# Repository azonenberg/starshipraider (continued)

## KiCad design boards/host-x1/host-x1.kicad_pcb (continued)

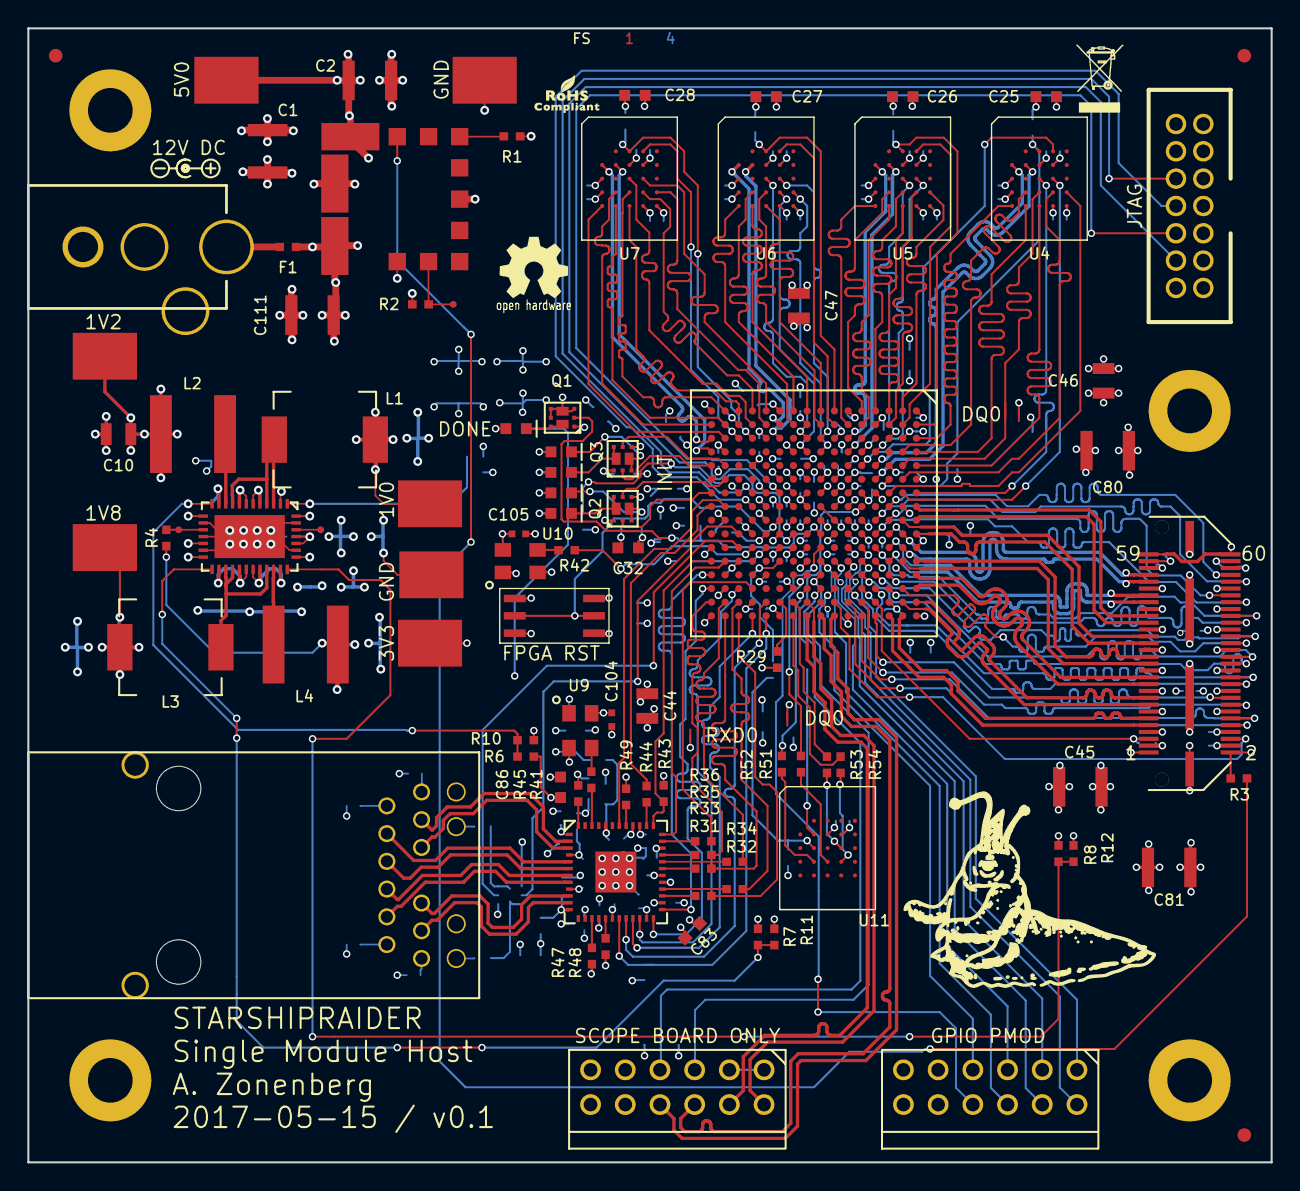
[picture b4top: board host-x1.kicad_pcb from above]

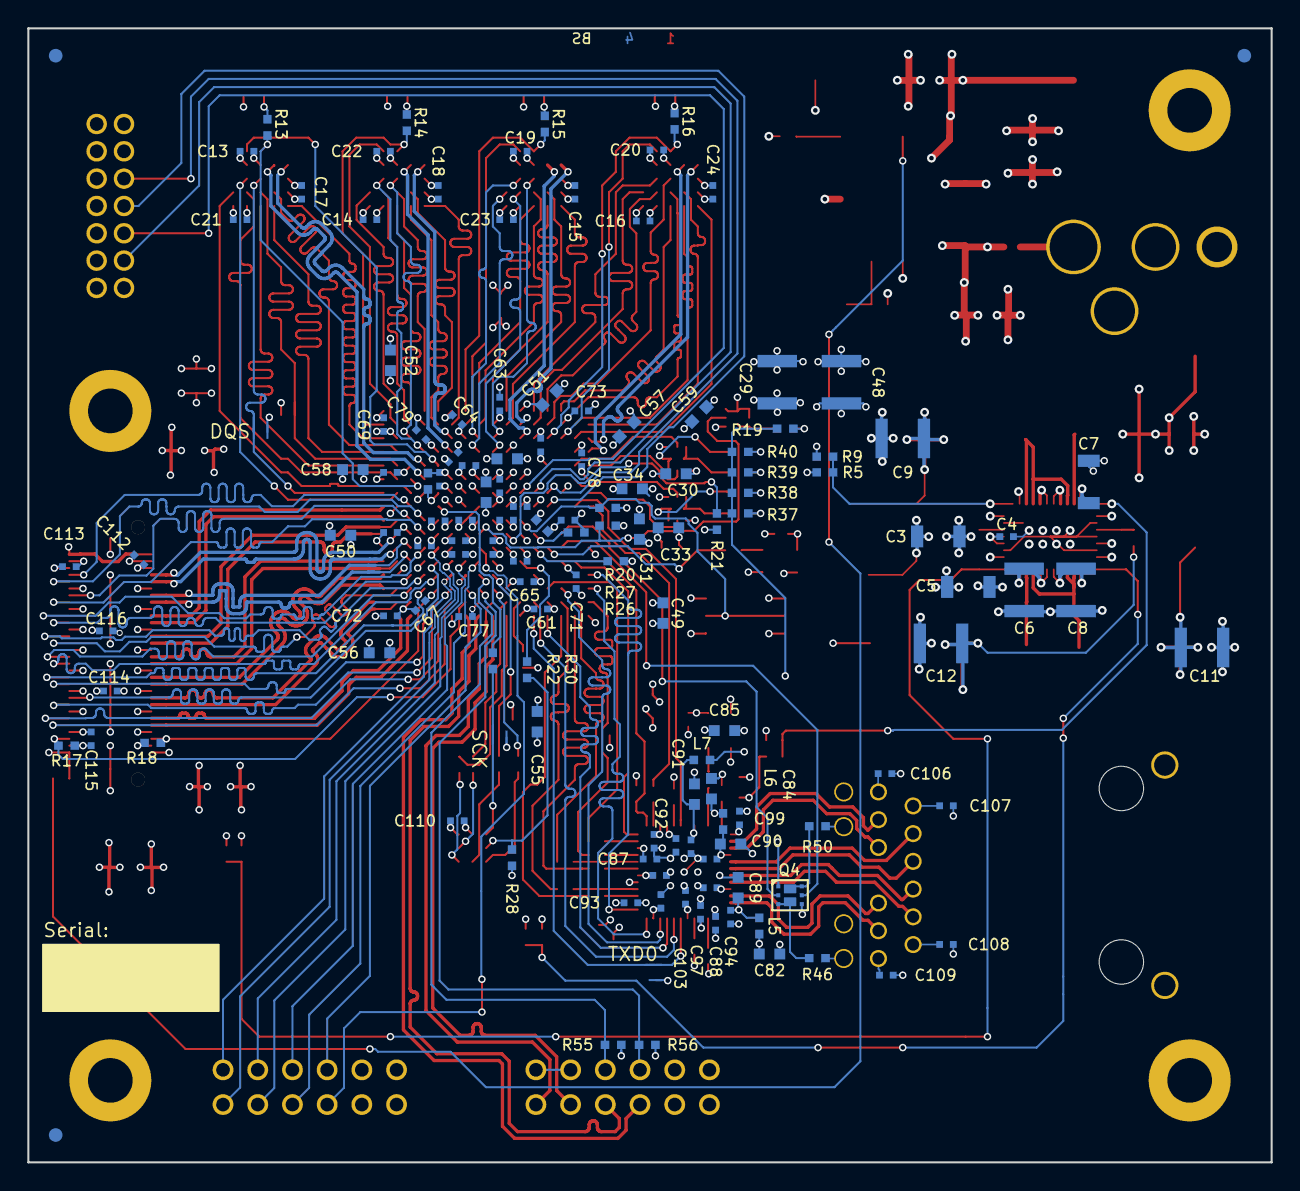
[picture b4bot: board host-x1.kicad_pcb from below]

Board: 4 copper layers, 91.0 x 83.0 mm, 251 parts (139 on the bottom side), 212 nets.

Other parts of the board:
C116: 0.1 uF; EIA_0402_CAP_NOSILK
FIDUCIAL_1MM, FIDUCIAL_1MM#2, FIDUCIAL_1MM#3, FIDUCIAL_1MM#4, FIDUCIAL_1MM#5, FIDUCIAL_1MM#6: VAL**; FIDUCIAL_1MM
M1: LOGO; LONGTHING-600DPI
M2: LOGO_ROHS; Logo_silk_ROHS_5x2.8mm
M3: LOGO_WEEE; Logo_silk_WEEE_3.4x5mm
M4, M5, M6, M7: HOLE; MECHANICAL_CLEARANCEHOLE_4_40

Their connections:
/3V3: C116.1; also elsewhere on the board
/GND: C116.2; also elsewhere on the board

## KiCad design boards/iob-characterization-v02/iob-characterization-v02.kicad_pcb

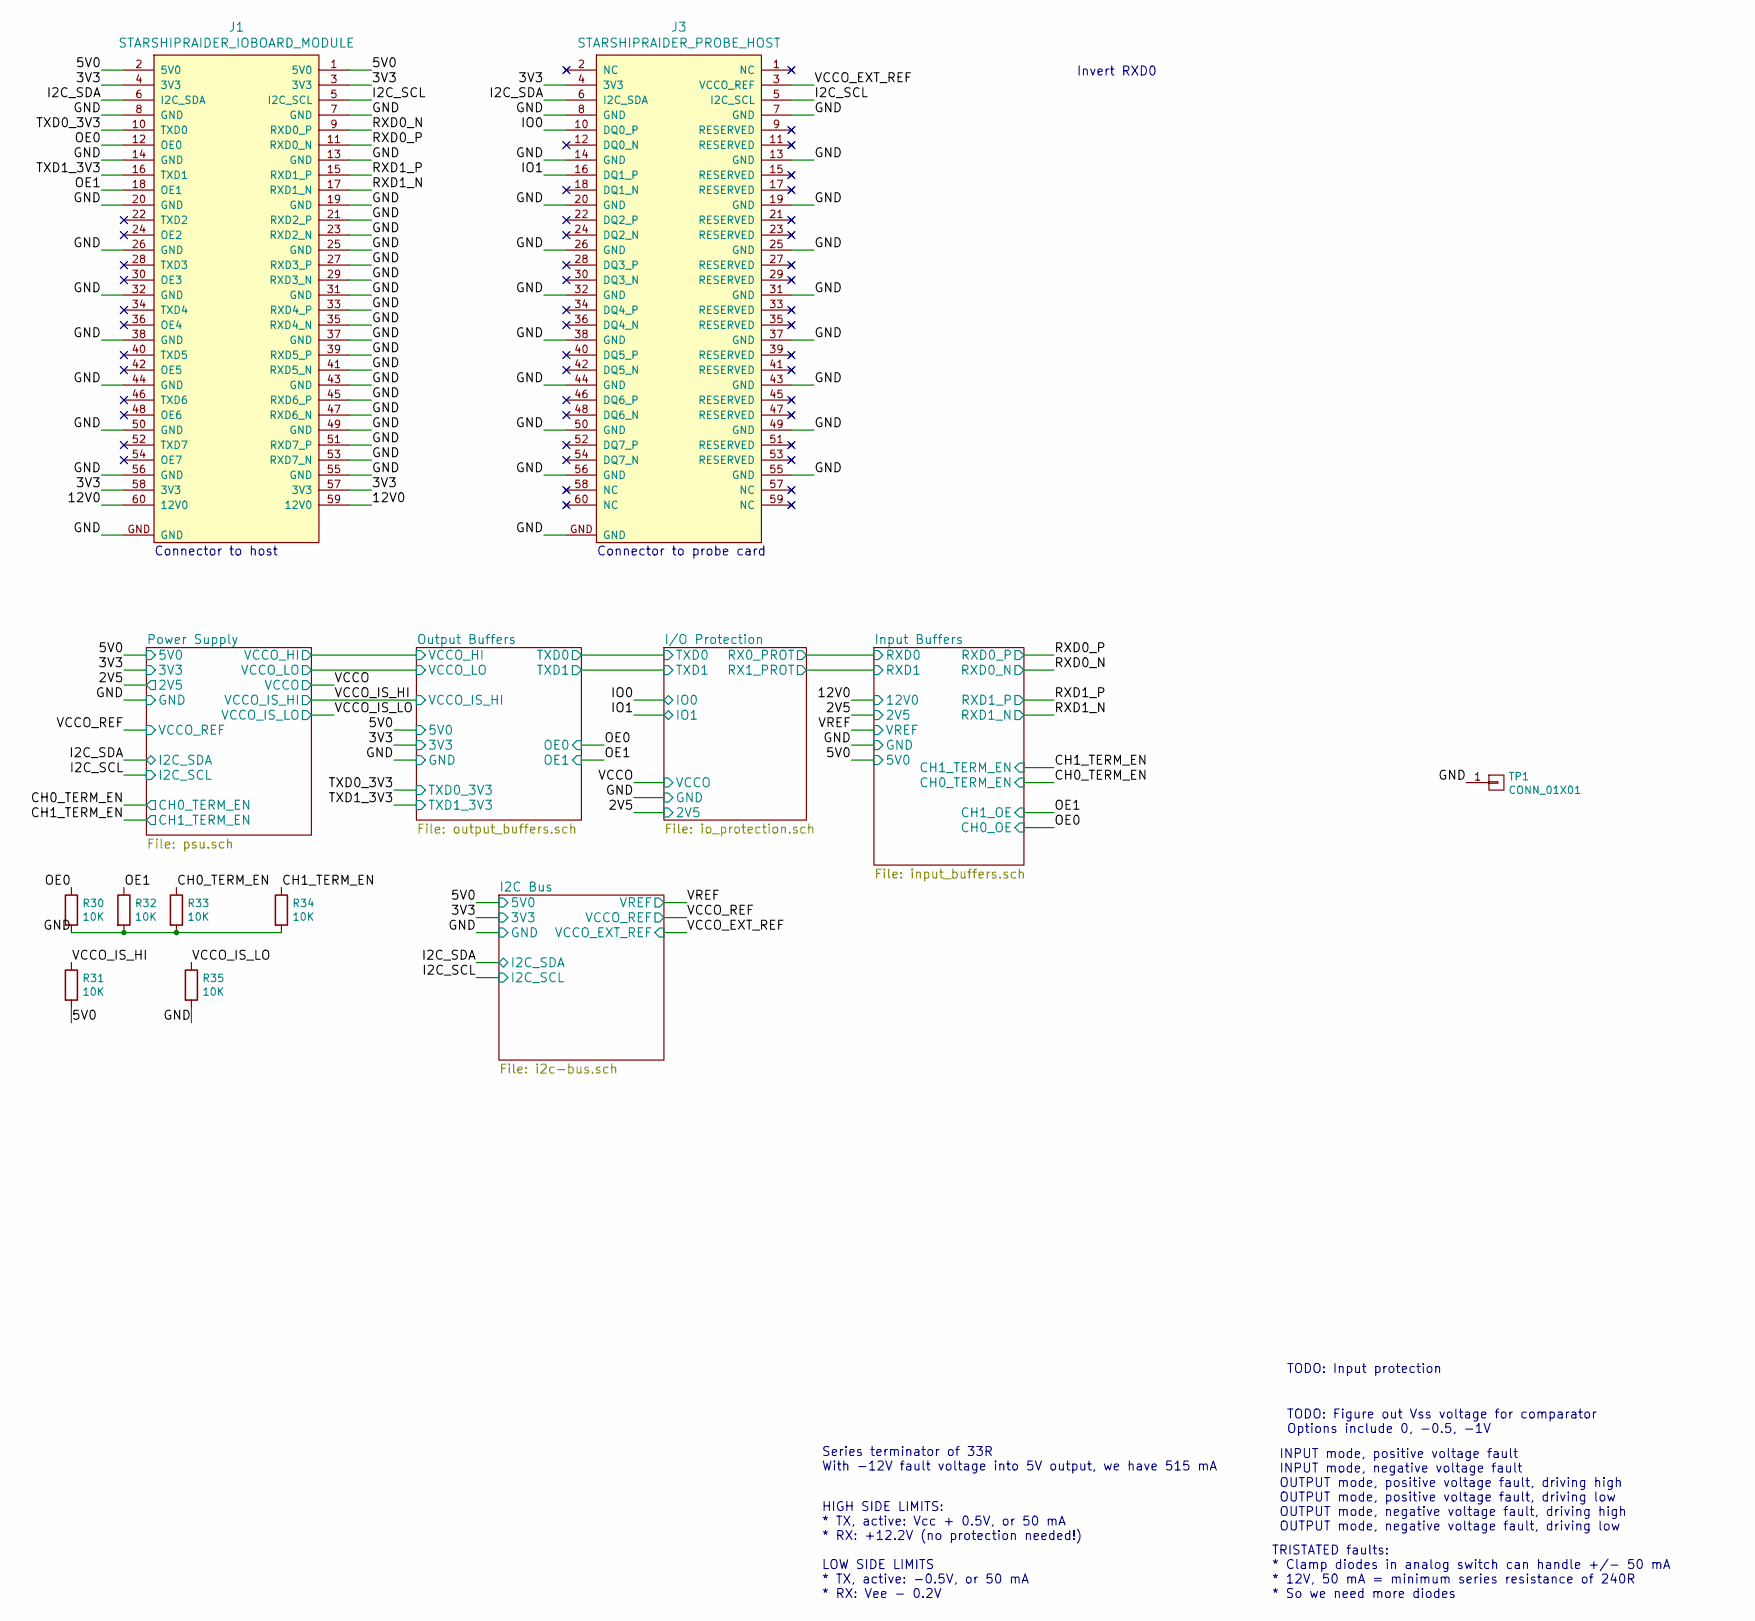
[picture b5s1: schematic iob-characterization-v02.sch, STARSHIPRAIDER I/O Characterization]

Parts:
J1: STARSHIPRAIDER_IOBOARD_MODULE; CONN_SAMTEC_QSH-030-01-L-D-A
J3: STARSHIPRAIDER_PROBE_HOST; CONN_SAMTEC_QTH-030-01-L-D-A
R30, R31, R32, R33, R34, R35: 10K; EIA_0402_RES_NOSILK
TP1: CONN_01X01; TESTPOINT_SMT_KEYSTONE_5016

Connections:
/3V3: J1.3 (3V3), J1.4 (3V3), J1.57 (3V3), J1.58 (3V3), J3.4 (3V3); also elsewhere on the board
/5V0: J1.1 (5V0), J1.2 (5V0), R31.2; also elsewhere on the board
/12V0: J1.59 (12V0), J1.60 (12V0); also elsewhere on the board
/CH0_TERM_EN: R33.1; also elsewhere on the board
/CH1_TERM_EN: R34.1; also elsewhere on the board
/GND: J1.7 (GND), J1.8 (GND), J1.13 (GND), J1.14 (GND), J1.19 (GND), J1.20 (GND), J1.21 (RXD2_P), J1.23 (RXD2_N), J1.25 (GND), J1.26 (GND), J1.27 (RXD3_P), J1.29 (RXD3_N), J1.31 (GND), J1.32 (GND), J1.33 (RXD4_P), J1.35 (RXD4_N), J1.37 (GND), J1.38 (GND), J1.39 (RXD5_P), J1.41 (RXD5_N), J1.43 (GND), J1.44 (GND), J1.45 (RXD6_P), J1.47 (RXD6_N), J1.49 (GND), J1.50 (GND), J1.51 (RXD7_P), J1.53 (RXD7_N), J1.55 (GND), J1.56 (GND), J1.GND, J3.7 (GND), J3.8 (GND), J3.13 (GND), J3.14 (GND), J3.19 (GND), J3.20 (GND), J3.25 (GND), J3.26 (GND), J3.31 (GND), J3.32 (GND), J3.37 (GND), J3.38 (GND), J3.43 (GND), J3.44 (GND), J3.49 (GND), J3.50 (GND), J3.55 (GND), J3.56 (GND), J3.GND, R30.2, R32.2, R33.2, R34.2, R35.2, TP1.1; also elsewhere on the board
/I2C_SCL: J1.5 (I2C_SCL), J3.5 (I2C_SCL); also elsewhere on the board
/I2C_SDA: J1.6 (I2C_SDA), J3.6 (I2C_SDA); also elsewhere on the board
/IO0: J3.10 (DQ0_P); also elsewhere on the board
/IO1: J3.16 (DQ1_P); also elsewhere on the board
/OE0: J1.12 (OE0), R30.1; also elsewhere on the board
/OE1: J1.18 (OE1), R32.1; also elsewhere on the board
/RXD0_N: J1.9 (RXD0_P); also elsewhere on the board
/RXD0_P: J1.11 (RXD0_N); also elsewhere on the board
/RXD1_N: J1.17 (RXD1_N); also elsewhere on the board
/RXD1_P: J1.15 (RXD1_P); also elsewhere on the board
/TXD0_3V3: J1.10 (TXD0); also elsewhere on the board
/TXD1_3V3: J1.16 (TXD1); also elsewhere on the board
/VCCO_EXT_REF: J3.3 (VCCO_REF); also elsewhere on the board
/VCCO_IS_HI: R31.1; also elsewhere on the board
/VCCO_IS_LO: R35.1; also elsewhere on the board

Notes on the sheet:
TODO: Input protection
TODO: Figure out Vss voltage for comparator Options include 0, -0.5, -1V
Connector to host
Connector to probe card
INPUT mode, positive voltage fault INPUT mode, negative voltage fault OUTPUT mode, positive voltage fault, driving high OUTPUT mode, positive voltage fault, driving low OUTPUT mode, negative voltage fault, driving high OUTPUT mode, negative voltage fault, driving low
TRISTATED faults: * Clamp diodes in analog switch can handle +/- 50 mA * 12V, 50 mA = minimum series resistance of 240R * So we need more diodes
Series terminator of 33R With -12V fault voltage into 5V output, we have 515 mA
HIGH SIDE LIMITS: * TX, active: Vcc + 0.5V, or 50 mA * RX: +12.2V (no protection needed!) LOW SIDE LIMITS * TX, active: -0.5V, or 50 mA * RX: Vee - 0.2V
Invert RXD0

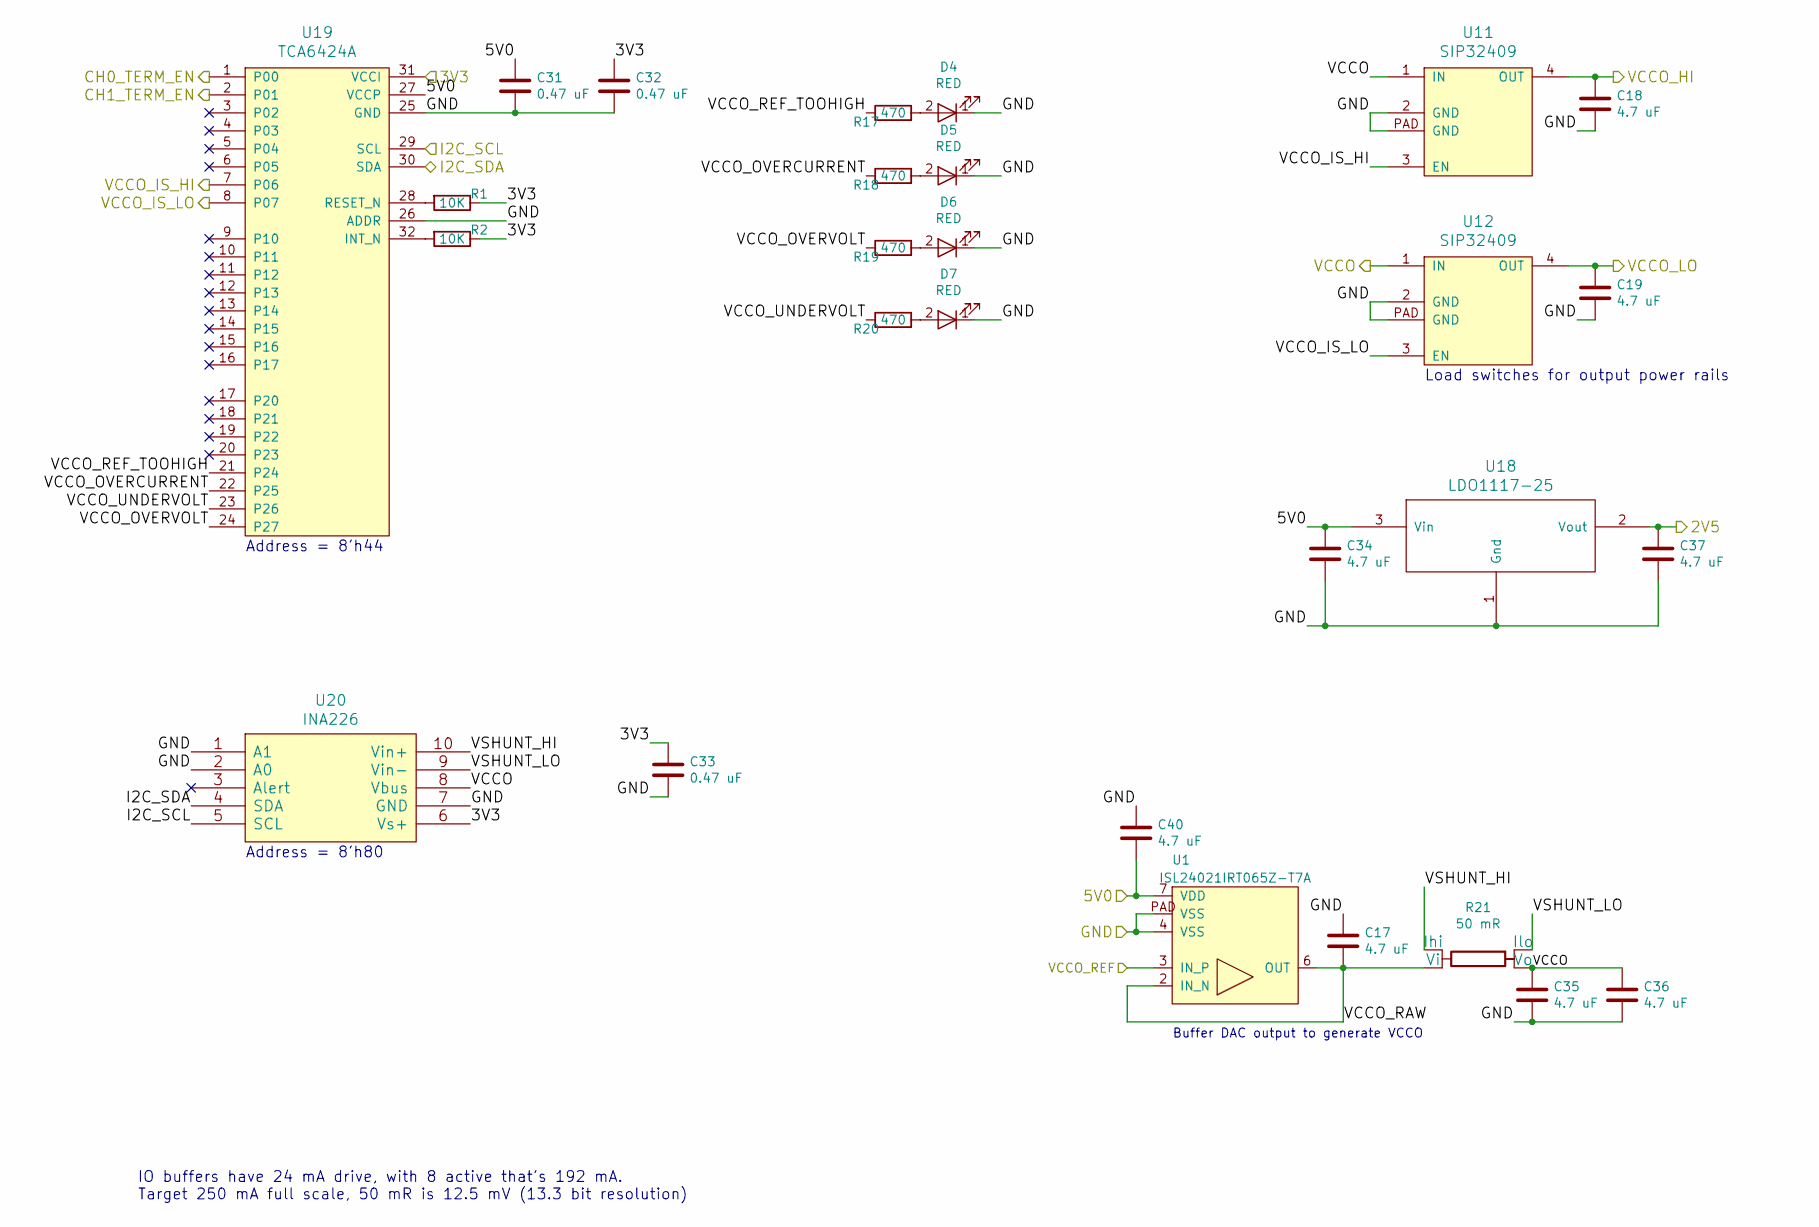
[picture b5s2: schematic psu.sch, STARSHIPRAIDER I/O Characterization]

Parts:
C17, C18, C19, C34, C35, C36, C37, C40: 4.7 uF; EIA_0603_CAP_NOSILK
C31, C32, C33: 0.47 uF; EIA_0402_CAP_NOSILK
D4, D5, D6, D7: RED; EIA_0603_LED
R1, R2: 10K; EIA_0402_CAP_NOSILK
R17, R18, R19, R20: 470; EIA_0402_RES_NOSILK
R21: 50 mR; OHMITE_LVK12
U1: ISL24021IRT065Z-T7A‎; DFN_8_0.65MM_3x3MM
U11, U12: SIP32409; DFN_4_0.5MM_1.6x1.2MM
U18: LDO1117-25; SOT223-4
U19: TCA6424A; QFN_32_0.5MM_5x5MM
U20: INA226; SOP_10_0.5MM_3MM

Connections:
/2V5: C37.1, U18.2 (Vout); also elsewhere on the board
/3V3: C32.1, C33.1, R1.1, R2.1, U19.31 (VCCI), U20.6 (Vs+); also elsewhere on the board
/5V0: C31.1, C34.1, C40.2, U1.7 (VDD), U18.3 (Vin), U19.27 (VCCP); also elsewhere on the board
/CH0_TERM_EN: U19.1 (P00); also elsewhere on the board
/CH1_TERM_EN: U19.2 (P01); also elsewhere on the board
/GND: C17.1, C18.2, C19.2, C31.2, C32.2, C33.2, C34.2, C35.2, C36.2, C37.2, C40.1, D4.1 (K), D5.1 (K), D6.1 (K), D7.1 (K), U1.4 (VSS), U1.PAD (VSS), U11.2 (GND), U11.PAD (GND), U12.2 (GND), U12.PAD (GND), U18.1 (Gnd), U19.25 (GND), U19.26 (ADDR), U20.1 (A1), U20.2 (A0), U20.7 (GND); also elsewhere on the board
/I2C_SCL: U19.29 (SCL), U20.5 (SCL); also elsewhere on the board
/I2C_SDA: U19.30 (SDA), U20.4 (SDA); also elsewhere on the board
/Output Buffers/VCCO_HI: C18.1, U11.4 (OUT); also elsewhere on the board
/Output Buffers/VCCO_LO: C19.1, U12.4 (OUT); also elsewhere on the board
/Power Supply/VCCO_OVERCURRENT: R18.1, U19.22 (P25)
/Power Supply/VCCO_OVERVOLT: R19.1, U19.24 (P27)
/Power Supply/VCCO_RAW: C17.2, R21.4 (Vi), U1.2 (IN_N), U1.6 (OUT)
/Power Supply/VCCO_REF_TOOHIGH: R17.1, U19.21 (P24)
/Power Supply/VCCO_UNDERVOLT: R20.1, U19.23 (P26)
/Power Supply/VSHUNT_HI: R21.3 (Ihi), U20.10 (Vin+)
/Power Supply/VSHUNT_LO: R21.1 (Ilo), U20.9 (Vin-)
/VCCO: C35.1, C36.1, R21.2 (Vo), U11.1 (IN), U12.1 (IN), U20.8 (Vbus); also elsewhere on the board
/VCCO_IS_HI: U11.3 (EN), U19.7 (P06); also elsewhere on the board
/VCCO_IS_LO: U12.3 (EN), U19.8 (P07); also elsewhere on the board
/VCCO_REF: U1.3 (IN_P); also elsewhere on the board
unnamed: D4.2 (A), R17.2
unnamed: D5.2 (A), R18.2
unnamed: D6.2 (A), R19.2
unnamed: D7.2 (A), R20.2
unnamed: R1.2, U19.28 (RESET_N)
unnamed: R2.2, U19.32 (INT_N)

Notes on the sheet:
Load switches for output power rails
Buffer DAC output to generate VCCO
Address = 8'h44
IO buffers have 24 mA drive, with 8 active that's 192 mA. Target 250 mA full scale, 50 mR is 12.5 mV (13.3 bit resolution)
Address = 8'h80

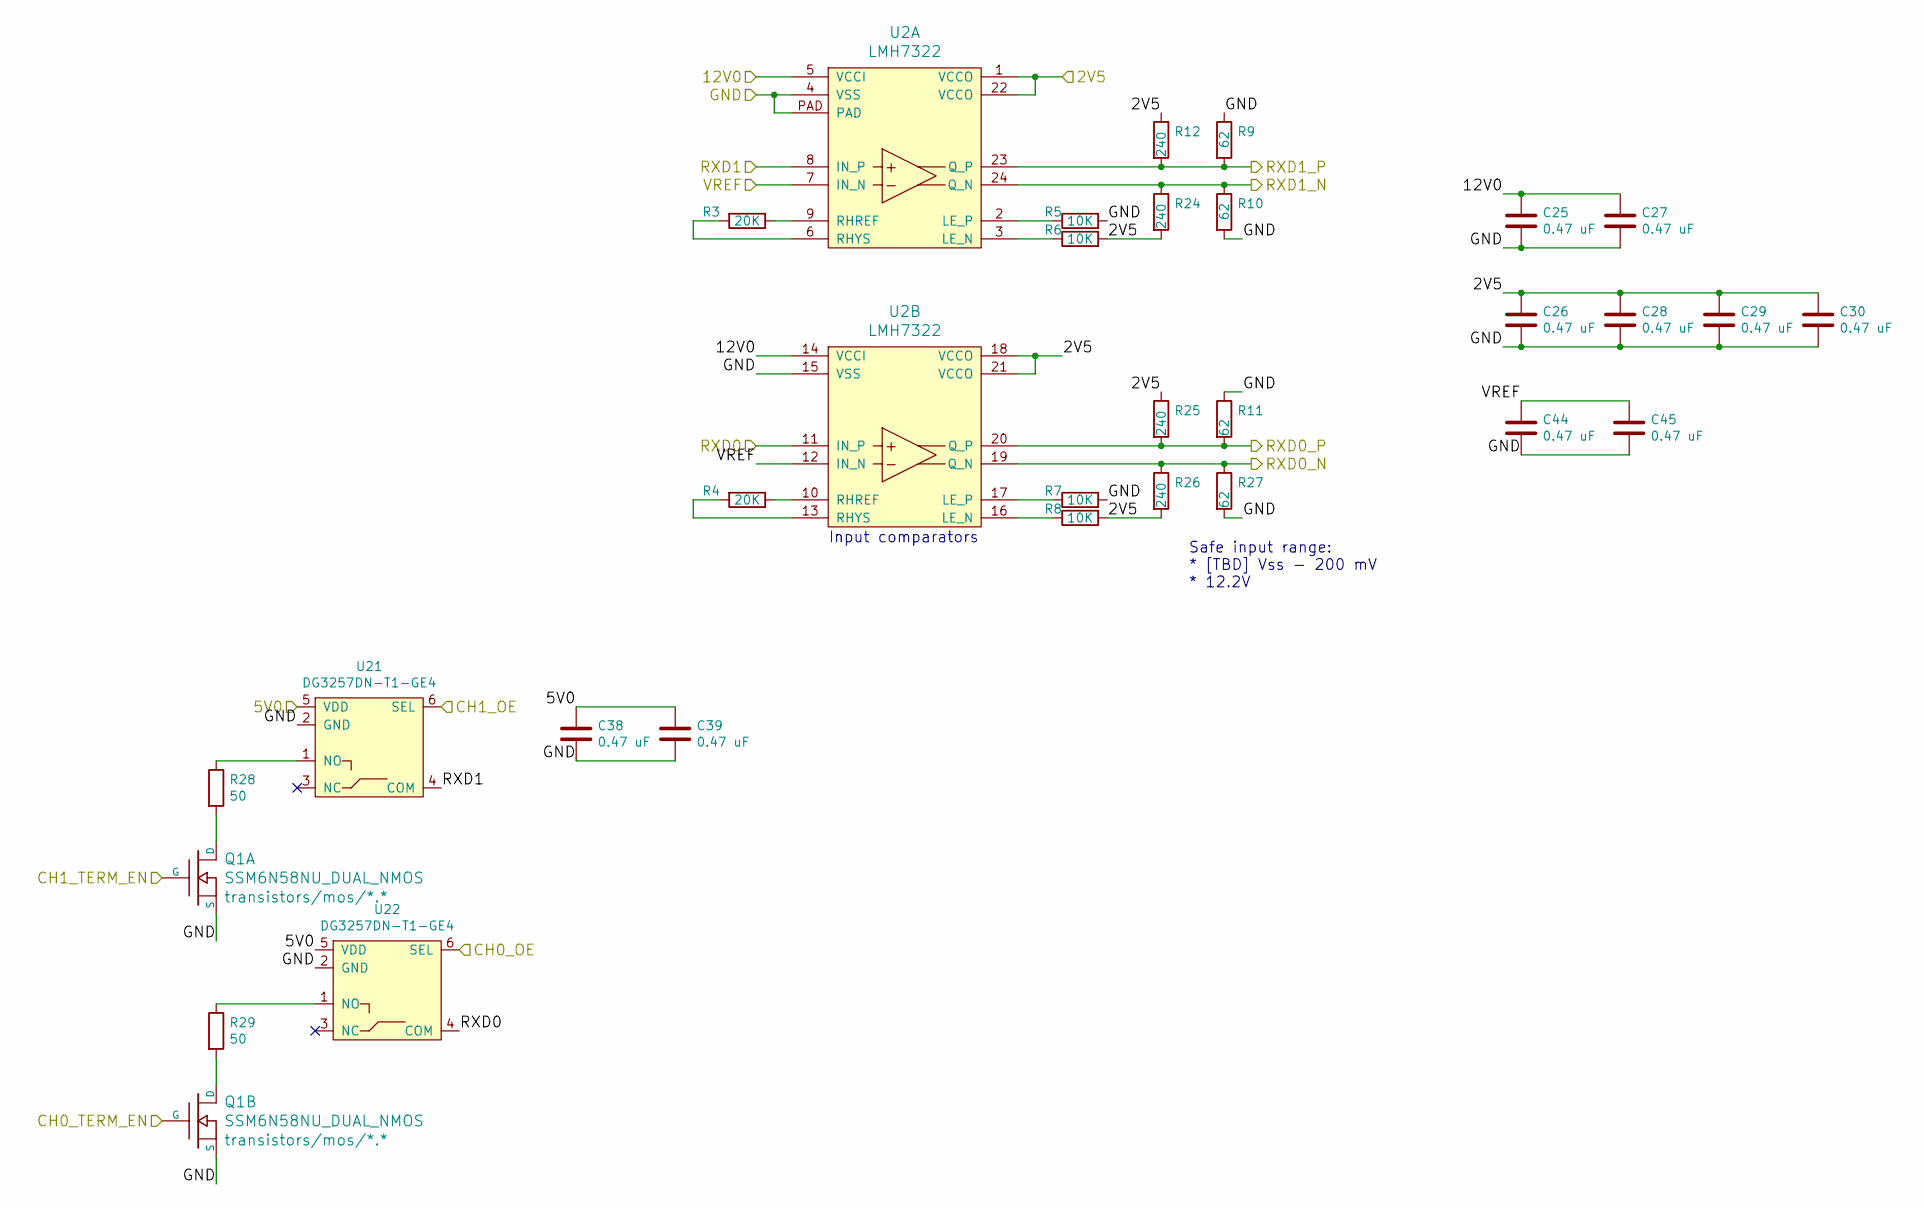
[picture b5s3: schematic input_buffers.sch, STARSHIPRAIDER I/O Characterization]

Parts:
C25, C26, C27, C28, C29, C30, C38, C39, C44, C45: 0.47 uF; EIA_0402_CAP_NOSILK
Q1: SSM6N58NU_DUAL_NMOS; DFN_6_0.65MM_2x2MM_GDS
R3, R4: 20K; EIA_0402_CAP_NOSILK
R5, R6, R7, R8: 10K; EIA_0402_CAP_NOSILK
R9, R10, R11, R27: 62; EIA_0402_RES_NOSILK
R12, R24, R25, R26: 240; EIA_0402_RES_NOSILK
R28, R29: 50; EIA_0201_RES_NOSILK
U2: LMH7322; QFN_24_0.5MM_4x4MM
U21, U22: DG3257DN-T1-GE4; DFN_6_0.35MM_1x1MM

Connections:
/2V5: C26.1, C28.1, C29.1, C30.1, R6.2, R8.2, R12.1, R24.2, R25.1, R26.2, U2.1 (VCCO), U2.18 (VCCO), U2.21 (VCCO), U2.22 (VCCO); also elsewhere on the board
/5V0: C38.1, C39.1, U21.5 (VDD), U22.5 (VDD); also elsewhere on the board
/12V0: C25.1, C27.1, U2.5 (VCCI), U2.14 (VCCI); also elsewhere on the board
/CH0_TERM_EN: Q1.G2 (G); also elsewhere on the board
/CH1_TERM_EN: Q1.G1 (G); also elsewhere on the board
/GND: C25.2, C26.2, C27.2, C28.2, C29.2, C30.2, C38.2, C39.2, C44.2, C45.2, Q1.S1 (S), Q1.S2 (S), R5.2, R7.2, R9.1, R10.2, R11.1, R27.2, U2.4 (VSS), U2.15 (VSS), U2.PAD, U21.2 (GND), U22.2 (GND); also elsewhere on the board
/I/O Protection/RX0_PROT: U2.11 (IN_P), U22.4 (COM); also elsewhere on the board
/I/O Protection/RX1_PROT: U2.8 (IN_P), U21.4 (COM); also elsewhere on the board
/OE0: U22.6 (SEL); also elsewhere on the board
/OE1: U21.6 (SEL); also elsewhere on the board
/RXD0_N: R26.1, R27.1, U2.19 (Q_N); also elsewhere on the board
/RXD0_P: R11.2, R25.2, U2.20 (Q_P); also elsewhere on the board
/RXD1_N: R10.1, R24.1, U2.24 (Q_N); also elsewhere on the board
/RXD1_P: R9.2, R12.2, U2.23 (Q_P); also elsewhere on the board
/VREF: C44.1, C45.1, U2.7 (IN_N), U2.12 (IN_N); also elsewhere on the board
unnamed: Q1.D1 (D), R28.2
unnamed: Q1.D2 (D), R29.2
unnamed: R3.1, U2.9 (RHREF)
unnamed: R3.2, U2.6 (RHYS)
unnamed: R4.1, U2.10 (RHREF)
unnamed: R4.2, U2.13 (RHYS)
unnamed: R5.1, U2.2 (LE_P)
unnamed: R6.1, U2.3 (LE_N)
unnamed: R7.1, U2.17 (LE_P)
unnamed: R8.1, U2.16 (LE_N)
unnamed: R28.1, U21.1 (NO)
unnamed: R29.1, U22.1 (NO)

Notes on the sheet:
Input comparators
Safe input range: * [TBD] Vss - 200 mV * 12.2V

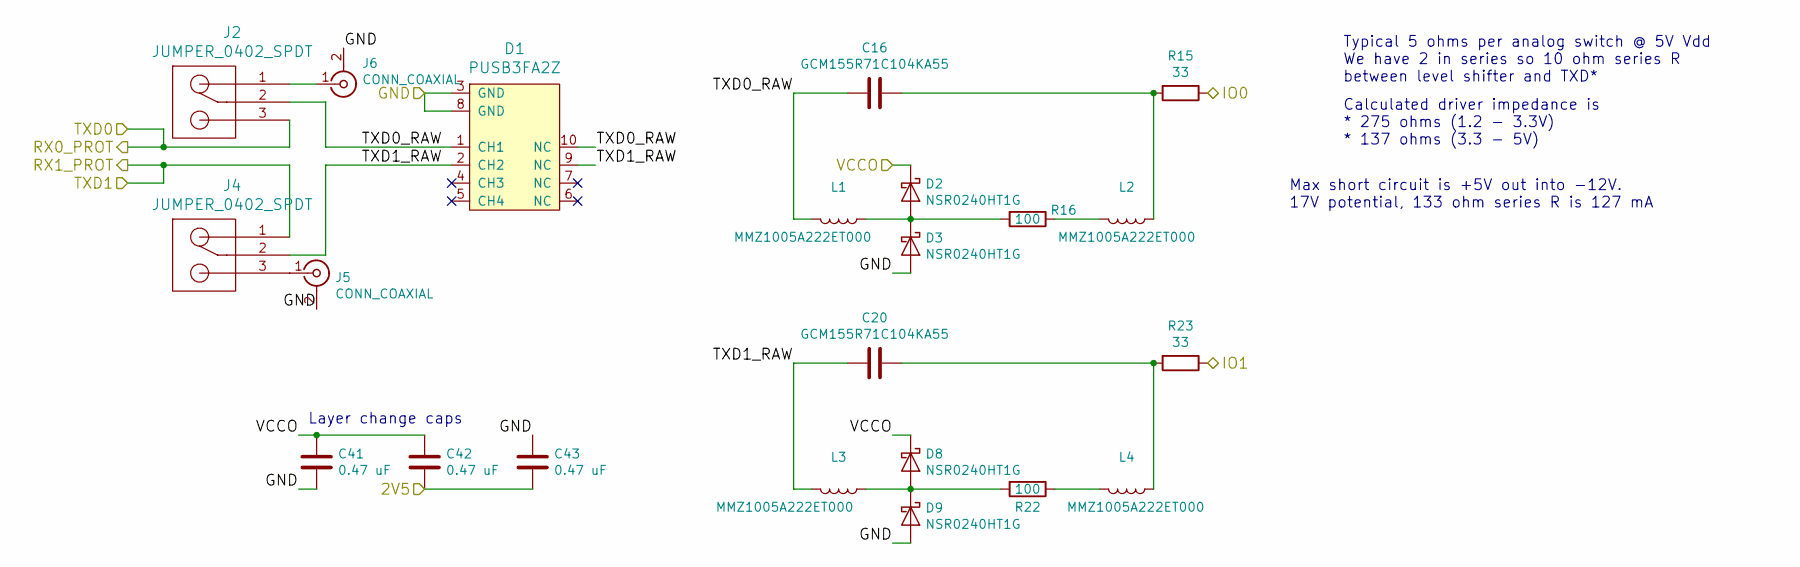
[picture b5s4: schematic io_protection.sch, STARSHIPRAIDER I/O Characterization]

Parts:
C16, C20: GCM155R71C104KA55; EIA_0402_CAP_NOSILK
C41, C42, C43: 0.47 uF; EIA_0402_CAP_NOSILK
D1: PUSB3FA2Z; DFN_10_0.5MM_2.5x1MM
D2, D3, D8, D9: ‎NSR0240HT1G‎; SOD323
J2, J4: JUMPER_0402_SPDT; EIA_0402_JUMPER
J5, J6: CONN_COAXIAL; CONN_MMCX_LINX_CONNMMCX002SMD
L1, L2, L3, L4: ‎MMZ1005A222ET000‎; EIA_0402_CAP_NOSILK
R15, R23: 33; EIA_0402_RES_NOSILK
R16, R22: 100; EIA_0402_RES_NOSILK

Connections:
/2V5: C42.2, C43.2; also elsewhere on the board
/GND: C41.2, C43.1, D1.3 (GND), D1.8 (GND), D3.2 (A), D9.2 (A), J5.2 (Ext), J6.2 (Ext); also elsewhere on the board
/I/O Protection/RX0_PROT: J2.3; also elsewhere on the board
/I/O Protection/RX1_PROT: J4.1; also elsewhere on the board
/I/O Protection/TXD0_RAW: C16.2, D1.1 (CH1), D1.10 (NC), J2.2, L1.2
/I/O Protection/TXD1_RAW: C20.2, D1.2 (CH2), D1.9 (NC), J4.2, L3.2
/IO0: R15.1; also elsewhere on the board
/IO1: R23.1; also elsewhere on the board
/VCCO: C41.1, C42.1, D2.1 (K), D8.1 (K); also elsewhere on the board
unnamed: C16.1, L2.1, R15.2
unnamed: C20.1, L4.1, R23.2
unnamed: D2.2 (A), D3.1 (K), L1.1, R16.2
unnamed: D8.2 (A), D9.1 (K), L3.1, R22.2
unnamed: J2.1, J6.1 (In)
unnamed: J4.3, J5.1 (In)
unnamed: L2.2, R16.1
unnamed: L4.2, R22.1

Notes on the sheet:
Typical 5 ohms per analog switch @ 5V Vdd We have 2 in series so 10 ohm series R between level shifter and TXD*
Calculated driver impedance is * 275 ohms (1.2 - 3.3V) * 137 ohms (3.3 - 5V)
Max short circuit is +5V out into -12V. 17V potential, 133 ohm series R is 127 mA
Layer change caps

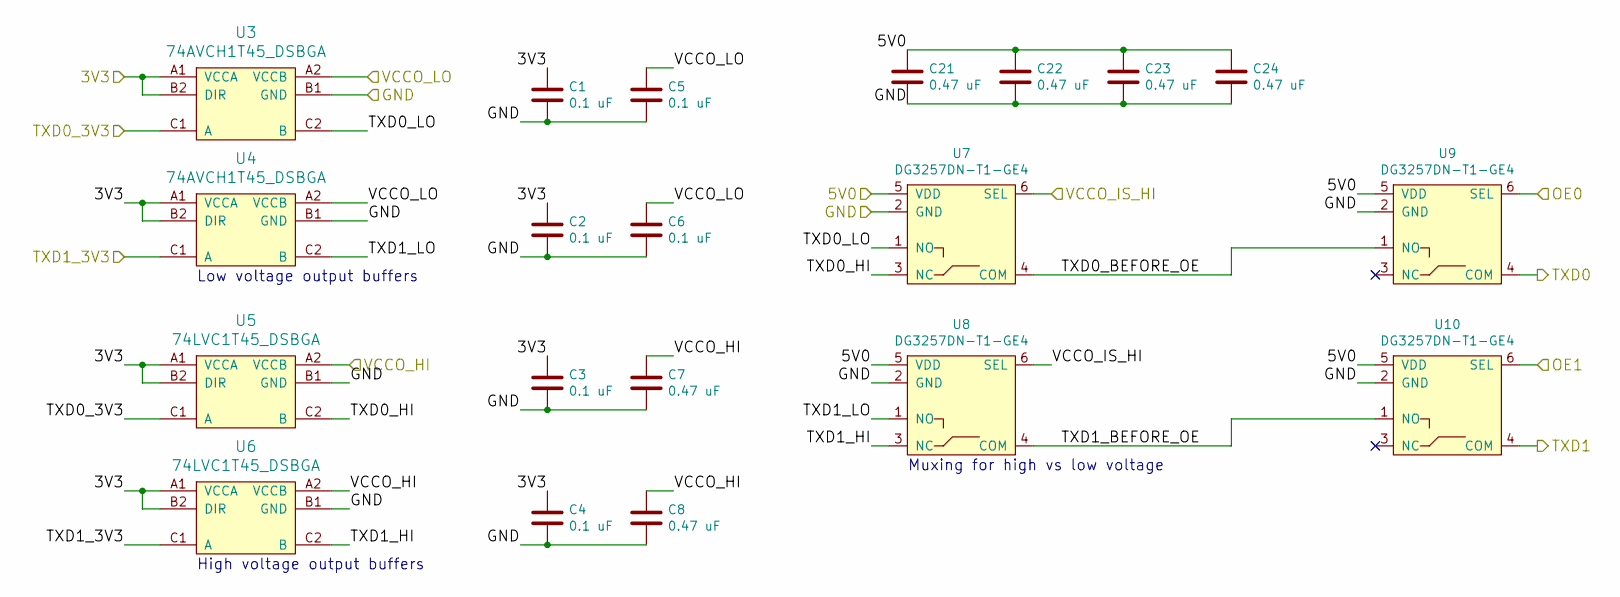
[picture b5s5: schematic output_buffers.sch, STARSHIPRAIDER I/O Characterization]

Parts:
C1, C2, C3, C4, C5, C6: 0.1 uF; EIA_0201_CAP_NOSILK
C7, C8, C21, C22, C23, C24: 0.47 uF; EIA_0402_CAP_NOSILK
U3, U4: 74AVCH1T45_DSBGA; BGA_6_1.5x0.9_0.5MM_TI_YZP
U5, U6: 74LVC1T45_DSBGA; BGA_6_1.5x0.9_0.5MM_TI_YZP
U7, U8, U9, U10: DG3257DN-T1-GE4; DFN_6_0.35MM_1x1MM

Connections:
/3V3: C1.1, C2.1, C3.1, C4.1, U3.A1 (VCCA), U3.B2 (DIR), U4.A1 (VCCA), U4.B2 (DIR), U5.A1 (VCCA), U5.B2 (DIR), U6.A1 (VCCA), U6.B2 (DIR); also elsewhere on the board
/5V0: C21.1, C22.1, C23.1, C24.1, U7.5 (VDD), U8.5 (VDD), U9.5 (VDD), U10.5 (VDD); also elsewhere on the board
/GND: C1.2, C2.2, C3.2, C4.2, C5.2, C6.2, C7.2, C8.2, C21.2, C22.2, C23.2, C24.2, U3.B1 (GND), U4.B1 (GND), U5.B1 (GND), U6.B1 (GND), U7.2 (GND), U8.2 (GND), U9.2 (GND), U10.2 (GND); also elsewhere on the board
/I/O Protection/RX0_PROT: U9.4 (COM); also elsewhere on the board
/I/O Protection/RX1_PROT: U10.4 (COM); also elsewhere on the board
/OE0: U9.6 (SEL); also elsewhere on the board
/OE1: U10.6 (SEL); also elsewhere on the board
/Output Buffers/TXD0_BEFORE_OE: U7.4 (COM), U9.1 (NO)
/Output Buffers/TXD0_HI: U5.C2 (B), U7.3 (NC)
/Output Buffers/TXD0_LO: U3.C2 (B), U7.1 (NO)
/Output Buffers/TXD1_BEFORE_OE: U8.4 (COM), U10.1 (NO)
/Output Buffers/TXD1_HI: U6.C2 (B), U8.3 (NC)
/Output Buffers/TXD1_LO: U4.C2 (B), U8.1 (NO)
/Output Buffers/VCCO_HI: C7.1, C8.1, U5.A2 (VCCB), U6.A2 (VCCB); also elsewhere on the board
/Output Buffers/VCCO_LO: C5.1, C6.1, U3.A2 (VCCB), U4.A2 (VCCB); also elsewhere on the board
/TXD0_3V3: U3.C1 (A), U5.C1 (A); also elsewhere on the board
/TXD1_3V3: U4.C1 (A), U6.C1 (A); also elsewhere on the board
/VCCO_IS_HI: U7.6 (SEL), U8.6 (SEL); also elsewhere on the board

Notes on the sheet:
Low voltage output buffers
High voltage output buffers
Muxing for high vs low voltage

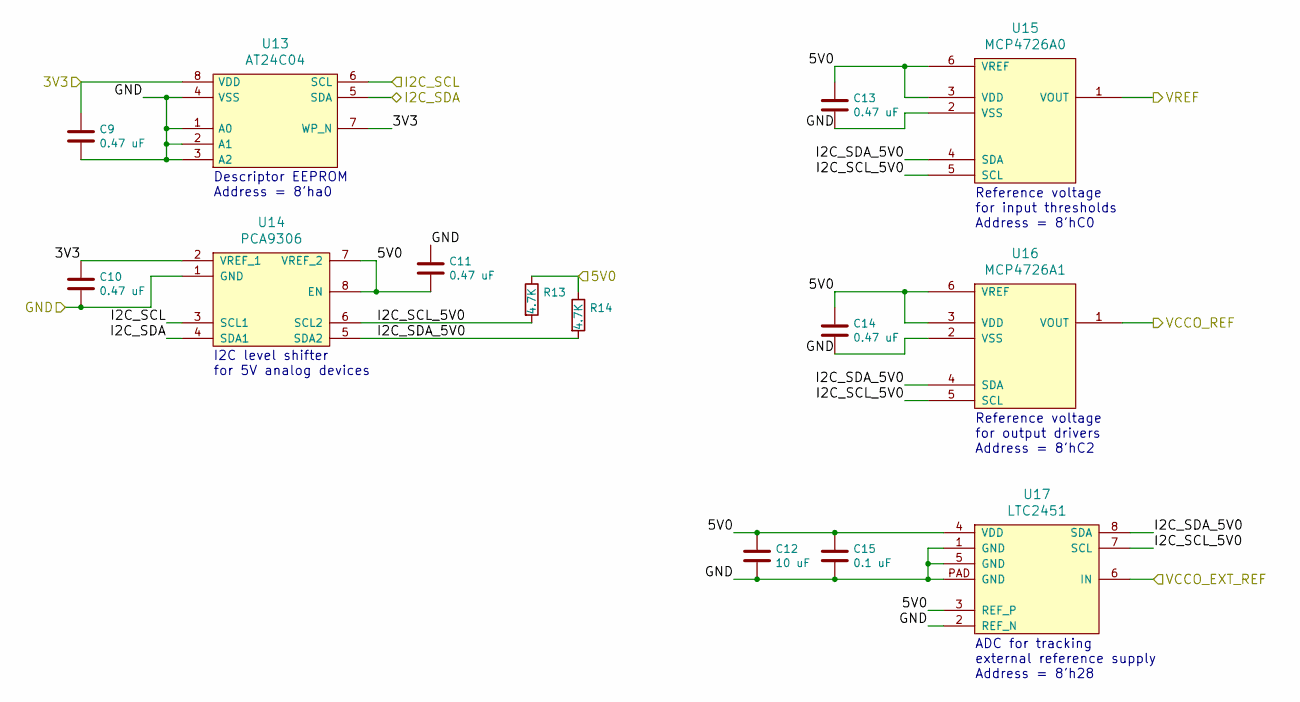
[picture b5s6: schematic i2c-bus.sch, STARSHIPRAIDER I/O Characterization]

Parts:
C9, C10, C11, C13, C14: 0.47 uF; EIA_0402_CAP_NOSILK
C12: 10 uF; EIA_0805_CAP_NOSILK
C15: 0.1 uF; EIA_0402_CAP_NOSILK
R13, R14: 4.7K; EIA_0402_RES_NOSILK
U13: AT24C04; DFN_8_0.5MM_2x3MM
U14: PCA9306; DFN_8_0.35MM_1x1.4MM
U15: MCP4726A0; SOT23_6
U16: MCP4726A1; SOT23_6
U17: LTC2451; DFN_8_0.5MM_2x3MM

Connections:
/3V3: C9.1, C10.1, U13.7 (WP_N), U13.8 (VDD), U14.2 (VREF_1); also elsewhere on the board
/5V0: C11.2, C12.1, C13.1, C14.1, C15.1, R13.1, R14.1, U14.7 (VREF_2), U14.8 (EN), U15.3 (VDD), U15.6 (VREF), U16.3 (VDD), U16.6 (VREF), U17.3 (REF_P), U17.4 (VDD); also elsewhere on the board
/GND: C9.2, C10.2, C11.1, C12.2, C13.2, C14.2, C15.2, U13.1 (A0), U13.2 (A1), U13.3 (A2), U13.4 (VSS), U14.1 (GND), U15.2 (VSS), U16.2 (VSS), U17.1 (GND), U17.2 (REF_N), U17.5 (GND), U17.PAD (GND); also elsewhere on the board
/I2C Bus/I2C_SCL_5V0: R13.2, U14.6 (SCL2), U15.5 (SCL), U16.5 (SCL), U17.7 (SCL)
/I2C Bus/I2C_SDA_5V0: R14.2, U14.5 (SDA2), U15.4 (SDA), U16.4 (SDA), U17.8 (SDA)
/I2C_SCL: U13.6 (SCL), U14.3 (SCL1); also elsewhere on the board
/I2C_SDA: U13.5 (SDA), U14.4 (SDA1); also elsewhere on the board
/VCCO_EXT_REF: U17.6 (IN); also elsewhere on the board
/VCCO_REF: U16.1 (VOUT); also elsewhere on the board
/VREF: U15.1 (VOUT); also elsewhere on the board

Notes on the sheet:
Descriptor EEPROM Address = 8'ha0
I2C level shifter for 5V analog devices
Reference voltage for input thresholds Address = 8'hC0
ADC for tracking external reference supply Address = 8'h28
Reference voltage for output drivers Address = 8'hC2

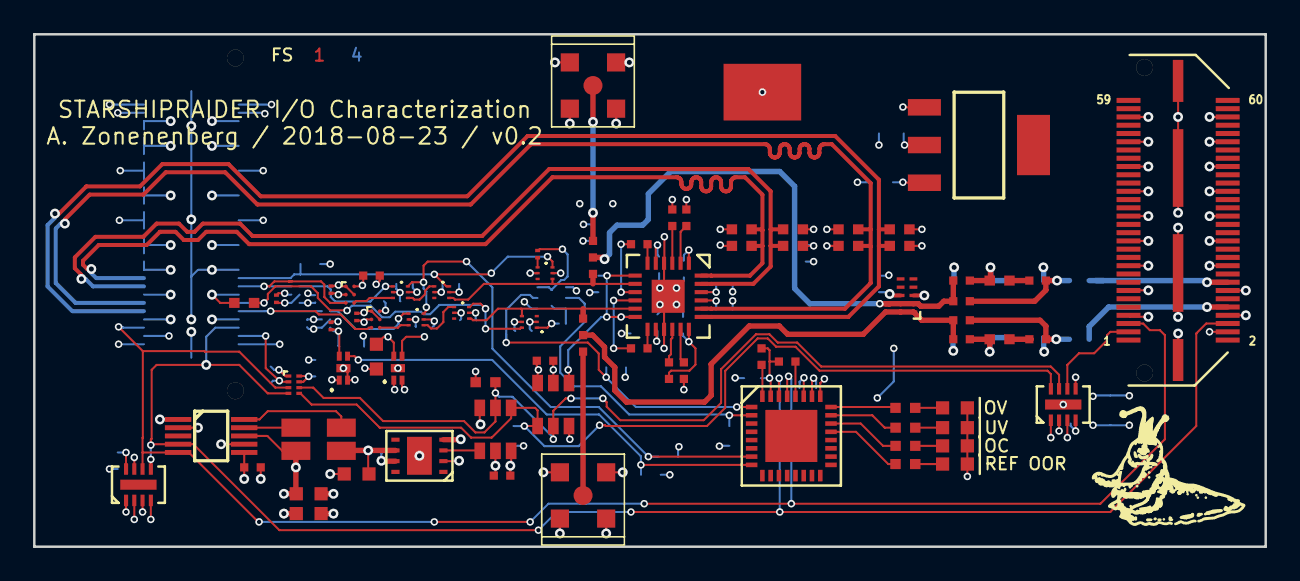
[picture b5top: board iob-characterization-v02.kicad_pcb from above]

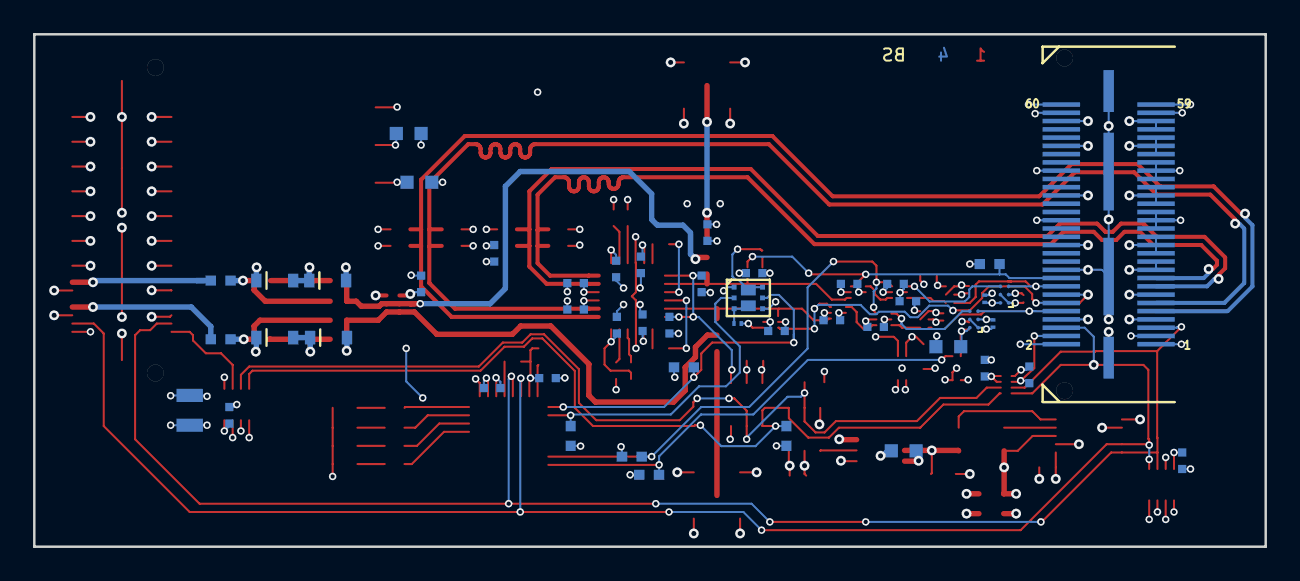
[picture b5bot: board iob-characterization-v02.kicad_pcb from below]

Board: 4 copper layers, 74.5 x 31.0 mm, 123 parts (48 on the bottom side), 72 nets.
